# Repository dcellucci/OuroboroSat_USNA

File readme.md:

# USNA Payload

Testing high-efficiency power transfer on a cubesat.

## Description

The OuroboroSat-USNA project is a collaboration between the NASA Ames Research Center Coded Structures Lab and The U.S. Naval Academy to produce an orbital experiment that tests a modular power system. 

The system consists of two OuroboroSat boards. Board 1 is connected to only solar panels, and board 2 is only connected to the spacecraft bus. The block diagram is as follows:

### Objectives

The objectives are this work are as follows

1. Test power transfer between two modules
   1. quantify transfer efficiency in the vacuum environment
   2. identify potential inefficiencies due to high temperature
2. Test indirect communications between two ouroboroSat boards
   1. quantify data and error rate for communication due to radiation
3. Quantify fatigue of power storage systems in the space environment
   1. degradation of overall capacity over many charge/discharge cycles

These objectives will establish critical parameters in the design of modular spacecraft busses, and will identify failure modes in the system due to operation in the space environment. The expected TRL of this system after the test will be 7, from TRL 6 shown in the sounding rocket test.

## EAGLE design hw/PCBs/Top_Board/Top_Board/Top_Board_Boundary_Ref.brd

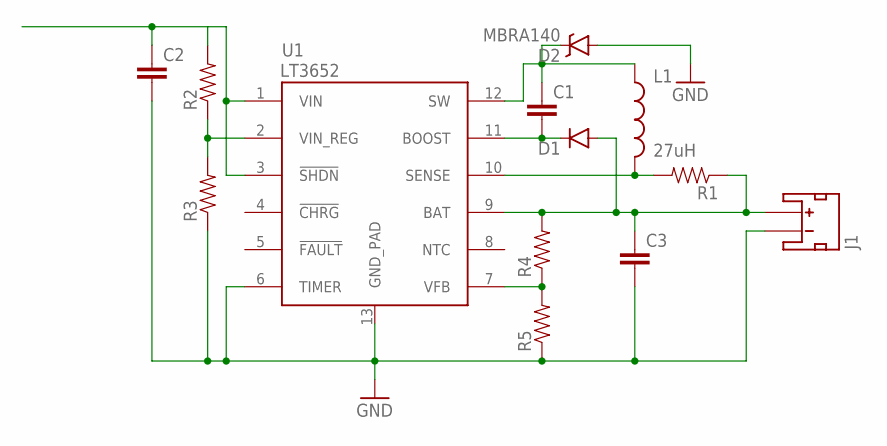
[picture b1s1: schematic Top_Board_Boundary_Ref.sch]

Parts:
C1, C2, C3: CAP0805; 0805
D1: DIODESMA; SMA-DIODE
D2: MBRA140; SMA-DIODE
J1: JST_2MM_MALE; JST-2-SMD
L1: 27uH; INDUCTOR_SDR1307
R1, R2, R3, R4, R5: RESISTOR0805-RES; 0805
U1: LT3652; MSOP-12_GND

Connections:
GND: C2.2, C3.2, D2.A, J1.1 (-), R3.1, R5.1, U1.6 (TIMER), U1.13 (GND_PAD)
unnamed: R4.1, R5.2, U1.7 (VFB)
unnamed: C3.1, D1.A, J1.2 (+), R1.1, R4.2, U1.9 (BAT)
unnamed: C1.1, D2.C, L1.P$1 (1), U1.12 (SW)
unnamed: C2.1, R2.2, U1.1 (VIN), U1.3 (!SHDN)
unnamed: R2.1, R3.2, U1.2 (VIN_REG)
unnamed: C1.2, D1.C, U1.11 (BOOST)
unnamed: L1.P$2 (2), R1.2, U1.10 (SENSE)

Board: 2 copper layers, 13 parts (0 on the bottom side), 8 nets, no tracks yet.

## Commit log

2016-08-03 Added Initial Mockup and 1.5 U design ref.
2016-08-03 added debug mockup images
2016-08-03 added specs markdown
2016-08-06 added top board physical specs
2016-12-05 better readme

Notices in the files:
parts and their libraries:
SparkFun-PowerIC: Licensing: Creative Commons ShareAlike 4.0 International - https://creativecommons.org/licenses/by-sa/4.0
